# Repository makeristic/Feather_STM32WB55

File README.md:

# Feather STM32WB55

A KiCad design for an STM32WB55CGU6 Bluetooth development board in the Adafruit Feather form factor, with USB-C, STEMMA QT, optional QSPI flash, and an optional SWD debug connector.

## WARNING: Work In Progress

This is a work in progress, it may not work at all.  :)

**Do not order the included fabrication files as a manufacturing release.** The [source audit](docs/code-audit-report.md) corrected a D10-to-ground short in the PCB source; the historical Gerbers and drill files still predate that fix. Layout, footprint, stackup, and electrical/RF review remain necessary before regenerating a complete fabrication set.

## Overview

I have several [Adafruit Feather](https://www.adafruit.com/category/943) boards, and Adafruit handily publish the [Feather Specification](https://learn.adafruit.com/adafruit-feather/feather-specification) here to make your own.  

I recently discovered the STM32WB series of microcontrollers which include Bluetooth connectivity and decided to build my own development board around it.  This repository is my first attempt at designing it and builds upon the great work of several sources (see Acknowledgements below).

The ultimate goal is to get this board working and running [CircuitPython](https://circuitpython.org/), once working I may do another revision with a focus on enabling more of the low power features of the STM32WB series.

## Features

* [STM32WB55CGU6](https://www.st.com/en/microcontrollers-microprocessors/stm32wb55cg.html) microcontroller
* Adafruit Feather compatible, with USB-C
* (Optional) QSPI-Dual flash module can be soldered to the back
* (Optional) ARM SWD 10-pin debug connector can be soldered on the back

## Notes

* The original fabrication notes specify a 4-layer board, 1mm thick with impedance-controlled traces, assuming the standard JLCPCB stackup. The committed PCB file currently records a thickness of 1.6mm; resolve this discrepancy with the board stackup before ordering.
* I've tried to standardise on 0.2mm tracks for signals, 0.3mm tracks for power.  VBUS and +BATT do have high-current tracks/pours to their respective pins to allow for powering things off-board like Neopixels.
* STMicroelectronics produce a custom matching network for this microcontroller [MLPF-WB55-01E3](https://www.st.com/en/emi-filtering-and-signal-conditioning/mlpf-wb55-01e3.html), the recommended PCB layout has been implemented here.
* The [Fractus Antenna](https://fractusantennas.com/compact-reach-xtend-nn01-102/) has a recommended layout which is implemented here.  The clearance area essentially takes up the entire tip of the board, though I have cheekily added the STEMMA QT connector, figuring it shouldn't have too big an impact.
* There is a lot of space around the center of the board, this is semi-intentional so I can extend the design with sensors, or an additional button.
* You can find my custom footprints etc. here [Makeristic-KiCad-Library](https://github.com/makeristic/Makeristic-KiCad-Library)

## Repository contents

* [KiCad project](Feather_STM32WB55.pro), [legacy schematic](Feather_STM32WB55.sch), [PCB](Feather_STM32WB55.kicad_pcb), and [netlist](Feather_STM32WB55.net).
* [Schematic PDF](Feather_STM32WB55-schematic.pdf) and [bill of materials](Feather_STM32WB55-BOM.csv).
* [Gerber and drill exports](gerber/), including both inner copper layers.
* [STM32CubeMX configuration](cubemx/cubemx.ioc). This is configuration input, not a complete firmware application or a CircuitPython port.
* [Vendor datasheets and layout references](datasheets/) and [design images](images/).
* [Recovered STM32/switch libraries](libraries/), [historical symbol cache](Feather_STM32WB55-cache.lib), and project [symbol](sym-lib-table)/[footprint](fp-lib-table) tables.

## Open or modify the design

1. Clone the repository and open `Feather_STM32WB55.pro` in KiCad. The PCB records KiCad **5.1.7**; the `.pro` and `.sch` files are legacy formats. Import into a copy if using a newer KiCad release.
2. Install the corresponding KiCad standard libraries and clone the Makeristic library alongside this repository. The project tables resolve that sibling checkout and the recovered board-local STM32/switch libraries. Keep the committed cache with the schematic so historical symbols remain available.
3. Resolve library warnings before editing. ANT1 and FL1 now have qualified Makeristic footprint identifiers, and their 3D-model paths plus the STM32 model path resolve through the sibling checkout. The [library notes](libraries/README.md) describe the recovery and its limits; restored assets have not been independently redesigned or electrically verified.
4. Review the RF layout, power path, stackup, and design-rule results before fabrication. Refill zones after source edits, then regenerate exports only after resolving the [audit findings](docs/code-audit-report.md). Existing images and fabrication files remain historical snapshots.

Nightly KiCad netlist checks need the [audit's cache-only export procedure](docs/code-audit-report.md): globally resolving the legacy USB symbol in nightly 10.99.0 omitted its shield pin from the export. No symbol/wiring workaround or bulk format migration was applied.

CircuitPython support remains the original project goal. No application firmware, flashing guide, or electrical/RF test report is included, and successful operation is not established by the files in this repository.

## Schematic

## PCB

## 3D Render

## TODO

* Improve the layout, potentially reassigning GPIO pins to simplify the traces

## Acknowledgements

* [Adafruit](https://www.adafruit.com/)
* [YouTube: Phil's Lab](https://www.youtube.com/c/PhilS94/videos)

## Feedback and related projects

Use [Issues](https://github.com/makeristic/Feather_STM32WB55/issues) for questions, build reports, missing-library information, or design corrections. Include the commit, KiCad version, and relevant component references. For design pull requests, explain the circuit change and identify any regenerated fabrication files.

Related projects: [Feather USB-C template](https://github.com/makeristic/Adafruit_Feather_USB-C), [STUSB4500 breakout](https://github.com/makeristic/STUSB4500_Breakout), and [Makeristic-KiCad-Library](https://github.com/makeristic/Makeristic-KiCad-Library).

## Licence

Michael Cutler's original design work and documentation are available under the [MIT licence](LICENSE). Vendor PDFs in `datasheets/`, third-party symbols, footprints and models (including embedded, recovered, and cached library elements), and third-party marks retain their respective owners' terms. KiCad symbols retain [CC BY-SA 4.0 with the KiCad exception](LICENSES/KiCad-Libraries.md). The MIT grant does not relicense those materials or imply endorsement by the acknowledged organisations.

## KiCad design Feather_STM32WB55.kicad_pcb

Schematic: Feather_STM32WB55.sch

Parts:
ANT1: NN01-102; FR05S1N0102; Manufacturer_Part_Number FR05-S1-N-0-102; Mouser Part Number 128-FR05-S1-N-0-102
C1, C2, C3: 10u; C_0805_2012Metric
C4: 1u; C_0805_2012Metric
C5: 1u; C_0603_1608Metric
C6: 10n; C_0603_1608Metric
C7: 4u7; C_0805_2012Metric
C8, C9, C10, C11, C12, C13: 100n; C_0603_1608Metric
C14: 100p; C_0603_1608Metric
D1, D4: LED; LED_0603_1608Metric
D2: B5819W; D_SOD-123; LCSC Part # C8598
D3: WS2812B; LED_SK6812MINI_PLCC4_3.5x3.5mm_P1.75mm
FL1: MLPF-WB55-01E3; MLPFWB5501E3; Manufacturer_Part_Number MLPF-WB55-01E3; Mouser Part Number 511-MLPF-WB55-01E3
J1: JST-SH Qwiic; JST_SH_SM04B-SRSS-TB_1x04-1MP_P1.00mm_Horizontal
J2: Conn_Battery; JST_PH_S2B-PH-SM4-TB_1x02-1MP_P2.00mm_Horizontal; Manufacturer Part # S2B-PH-SM4-TB(LF)(SN); LCSC Part # C295747
J3: Conn_ARM_JTAG_SWD_10; PinHeader_2x05_P1.00mm_Vertical_SMD
J4: Conn_Right; PinHeader_1x12_P2.54mm_Vertical
J5: USB_C_Receptacle_USB2.0; USB_C_Receptacle_XKB_U262-16XN-4BVC11; Manufacturer Part # U262-161N-4BVC11; LCSC Part # C319148
J6: Conn_Left; PinHeader_1x16_P2.54mm_Vertical
L1: 39n; L_0603_1608Metric
Q1: NTR4171PT1G; SOT-23; Manufacturer Part # NTR4171PT1G; LCSC Part # C558218
R1, R4: 1k; R_0603_1608Metric
R2, R3, R5: 10k; R_0603_1608Metric
R6, R10: 100k; R_0603_1608Metric
R7, R8, R9: 5k1; R_0603_1608Metric
SW1: SMD-BUTTON-TOP-DHT-4235A_4P-4.2X3.2MM_; SW4-SMD-4.2X3.2X2.5MM; MPN DHT-4235A
U1: MCP73831-2-OT; SOT-23-5
U2: AP2112K-3.3; SOT-23-5
U3: STM32WB55CGU6; STMicroelectronics-STM32WB55CGU6-IPC_B; mouser part number 511-STM32WB55CGU6; digikey description ULTRA-LOW-POWER DUAL CORE ARM CO
U4: USBLC6-2SC6; SOT-23-6
U5: Flash SOIC-8; SOIC-8_3.9x4.9mm_P1.27mm
Y1: 32Mhz; Crystal_SMD_3225-4Pin_3.2x2.5mm; Manufacturer Part # X1E000021016300; LCSC Part # C91742

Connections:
+3.3VA: C5.1, C6.1, J6.3, L1.1, U3.8 (VDDA)
+BATT: C1.1, J2.2, J4.1, Q1.3 (D), U1.3 (VBAT)
A0: J6.5, U3.43 (PB3)
A1: J6.6, U3.2 (PC14-OSC32_IN)
A2: J6.7, U3.3 (PC15-OSC32_OUT)
A3: J6.8, U3.9 (PA0)
A4: J6.9, U3.13 (PA4)
A5: J6.10, U3.14 (PA5)
ANT_OUT: ANT1.1, FL1.1
BOOT0: J6.16, R10.1, U3.4 (PH3-BOOT0)
D5: J4.10, U3.28 (PB0)
D6: J4.9, U3.29 (PB1)
D8_NEOPIXEL: D3.4 (DIN), U3.42 (PA15)
D9: J4.8, U3.30 (PE4)
D10: J4.7, U3.19 (PB2)
D11: J4.6, U3.17 (PA8)
D12: J4.5, U3.16 (PA7)
D13: J4.4, R4.1, U3.15 (PA6)
EN: J4.2, R5.2, U2.3 (EN)
GND: C1.2, C2.2, C3.2, C4.2, C5.2, C6.2, C7.2, C8.2, C9.2, C10.2, C11.2, C12.2, C13.2, C14.2, D3.3 (VSS), D4.1 (K), FL1.2, FL1.4, FL1.5, FL1.6, J1.1, J2.1, J3.3 (GND), J3.5 (GND), J3.9 (GNDDetect), J5.A1 (GND), J5.A12 (GND), J5.B1 (GND), J5.B12 (GND), J5.S1 (SHIELD), J6.4, R6.2, R7.2, R8.2, R9.2, R10.2, SW1.3 (B0), SW1.4 (B1), U1.2 (VSS), U2.2 (GND), U3.22 (VSSRF), U3.32 (VSSSMPS), U3.49 (EP), U4.2 (GND), U5.4 (GND), Y1.2, Y1.4
HSE_IN: U3.25 (OSC_IN), Y1.1
HSE_OUT: U3.24 (OSC_OUT), Y1.3
I2C_SCL: J1.4, J4.11, R2.2, U3.18 (PA9)
I2C_SDA: J1.3, J4.12, R3.2, U3.36 (PA10)
NRST: J3.10 (~RESET~), J6.1, SW1.1 (A0), SW1.2 (A1), U3.7 (~RST~)
unnamed: C2.1, D2.1 (K), Q1.2 (S), R5.1, U2.1 (VIN)
unnamed: D1.1 (K), R1.1
unnamed: D4.2 (A), R4.2
unnamed: J5.A5 (CC1), R9.1
unnamed: J5.B5 (CC2), R8.1
unnamed: R1.2, U1.1 (STAT)
unnamed: R7.1, U1.5 (PROG)
QSPI_CLK: U3.12 (PA3), U5.6 (SCK)
QSPI_IO0: U3.6 (PB9), U5.5 (SI/IO0)
QSPI_IO1: U3.5 (PB8), U5.2 (SO/IO1)
QSPI_NSC: U3.11 (PA2), U5.1 (~CS)
RF_OUT: FL1.3, U3.21 (RF1)
SPI_MISO: J6.13, U3.44 (PB4)
SPI_MOSI: J6.12, U3.45 (PB5)
SPI_SCK: J6.11, U3.10 (PA1)
SWDCLK: J3.4 (SWDCLK/TCK), U3.41 (PA14)
SWDIO: J3.2 (SWDIO/TMS), U3.39 (PA13)
USART1_RX: J6.14, U3.47 (PB7)
USART1_TX: J6.15, U3.46 (PB6)
USB_CONN_D+: J5.A6 (D+), J5.B6 (D+), U4.3 (I/O2)
USB_CONN_D-: J5.A7 (D-), J5.B7 (D-), U4.1 (I/O1)
USB_D+: U3.38 (PA12), U4.4 (I/O2)
USB_D-: U3.37 (PA11), U4.6 (I/O1)
VBUS: D1.2 (A), D2.2 (A), J4.3, J5.A4 (VBUS), J5.A9 (VBUS), J5.B4 (VBUS), J5.B9 (VBUS), Q1.1 (G), R6.1, U1.4 (VDD), U4.5 (VBUS)
VDD: C3.1, C4.1, C7.1, C8.1, C9.1, C10.1, C11.1, C12.1, C13.1, C14.1, D3.1 (VDD), J1.2, J3.1 (VTref), J6.2, L1.2, R2.1, R3.1, U2.5 (VOUT), U3.1 (VBAT), U3.20 (VDD), U3.23 (VDDRF), U3.31 (VFBSMPS), U3.33 (VLXSMPS), U3.34 (VDDSMPS), U3.35 (VDD), U3.40 (VDDUSB), U3.48 (VDD), U5.3 (~WP~/IO2), U5.7 (~HOLD~/IO3), U5.8 (VCC)

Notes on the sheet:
Connectors etc.
Microcontroller
Power
Misc

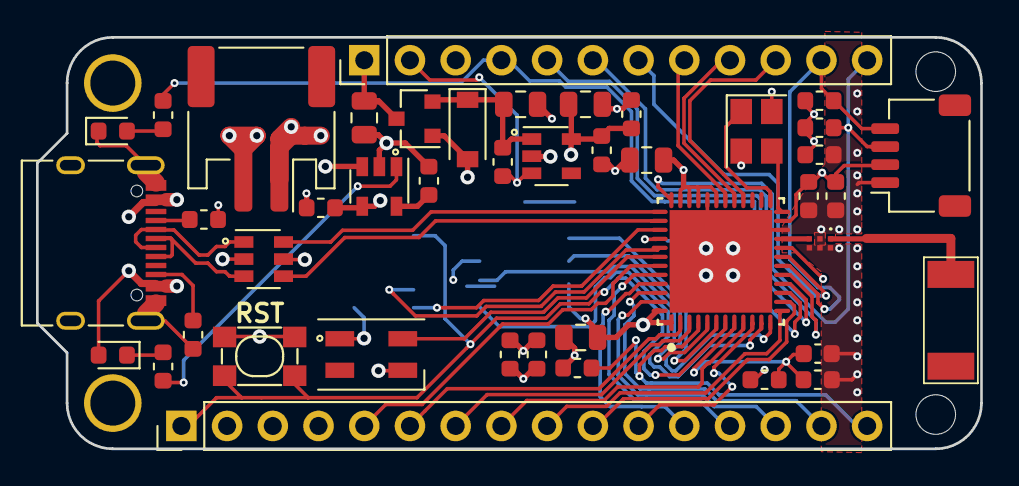
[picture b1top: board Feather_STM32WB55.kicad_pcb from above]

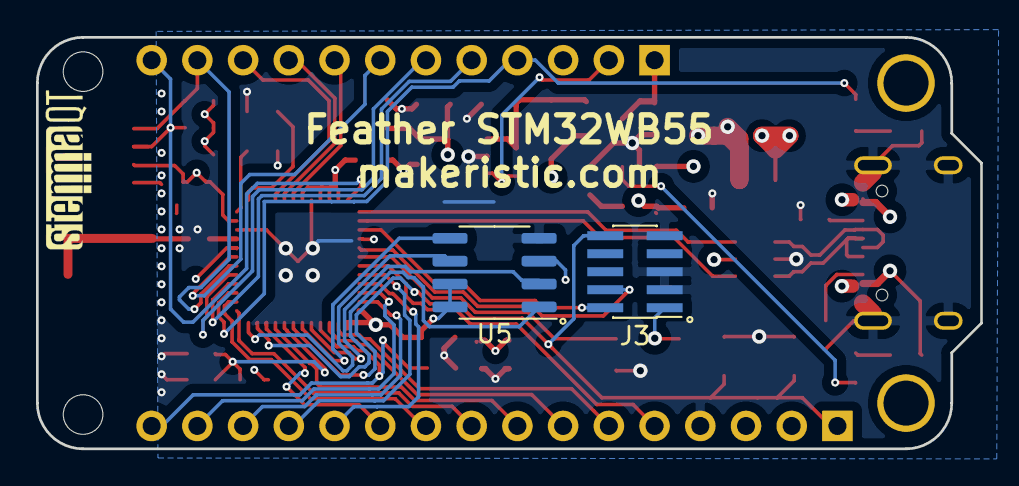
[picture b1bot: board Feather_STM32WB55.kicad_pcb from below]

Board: 4 copper layers, 52.5 x 22.9 mm, 45 parts (2 on the bottom side), 50 nets.

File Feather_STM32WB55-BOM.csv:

Reference, Value, Footprint, Datasheet, LCSC Part #, Manufacturer Part #, RAM size, ambient temperature range high, ambient temperature range low, automotive, category, core architecture, data bus width, device class L1, device class L2, device class L3, digikey description, digikey part number, frequency, height, interface, lead free, library id, manufacturer, max junction temp, max supply voltage, memory size, memory type, min supply voltage, mouser part number, number of A/D converters, number of ADC channels, number of I/Os, number of I2C channels, number of PWM channels, number of SPI channels, number of UART channels, number of USB channels, number of cores, number of timers/counters, package, rohs, standoff height, temperature range high, temperature range low, MPN, SKU, Description, Height, Manufacturer_Name, Manufacturer_Part_Number, Mouser Part Number, Mouser Price/Stock, Arrow Part Number, Arrow Price/Stock
"J4","Conn_Right","Connector_PinHeader_2.54mm:PinHeader_1x12_P2.54mm_Vertical","~"
"J6","Conn_Left","Connector_PinHeader_2.54mm:PinHeader_1x16_P2.54mm_Vertical","~"
"J2","Conn_Battery","Connector_JST:JST_PH_S2B-PH-SM4-TB_1x02-1MP_P2.00mm_Horizontal","https://datasheet.lcsc.com/szlcsc/2004071131_JST-Sales-Ameri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","C295747","S2B-PH-SM4-TB(LF)(SN)","","","","","","","","","","","","","","","","","","","","","","","","","","","","","","","","","","","","","","","","","","","","","","","","",""
"J5","USB_C_Receptacle_USB2.0","Connector_USB:USB_C_Receptacle_XKB_U262-16XN-4BVC11","https://datasheet.lcsc.com/szlcsc/2002271811_XKB-Enterprise-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","C319148","U262-161N-4BVC11","","","","","","","","","","","","","","","","","","","","","","","","","","","","","","","","","","","","","","","","","","","","","","","","",""
"U3","STM32WB55CGU6","IC_STMicroelectronics_STM32WB55CGU6:STMicroelectronics-STM32WB55CGU6-IPC_B","https://www.st.com/resource/en/datasheet/stm32wb55cg.pdf","","","256KBytes","+85°C","-40°C","No","IC","ARM Cortex-M4","32bits","Integrated Circuits (ICs)","Embedded Processors and Controllers","Microcontrollers","ULTRA-LOW-POWER DUAL CORE ARM CO","497-18489-ND","64MHz","0.65mm","I2C,SPI,UART,USART,2-Wire,USB,IrDA,Other","Yes","7cd8443577175ffa","STMicroelectronics","+105°C","3.6V","1MBytes","FLASH","1.71V","511-STM32WB55CGU6","1","13","30","2","14","1","2","1","1","6","UFQFPN48","Yes","0mm","+105°C","-40°C","","","","","","","","","",""
"J3","Conn_ARM_JTAG_SWD_10","Connector_PinHeader_1.00mm:PinHeader_2x05_P1.00mm_Vertical_SMD","http://infocenter.arm.com/help/topic/com.arm.doc.ddi0314h/DD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"
"U4","USBLC6-2SC6","Package_TO_SOT_SMD:SOT-23-6","https://www.st.com/resource/en/datasheet/usblc6-2.pdf"
"C13","100n","Capacitor_SMD:C_0603_1608Metric","~"
"Y1","32Mhz","Crystal:Crystal_SMD_3225-4Pin_3.2x2.5mm","https://datasheet.lcsc.com/szlcsc/Seiko-Epson-X1E00002101630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","C91742","X1E000021016300","","","","","","","","","","","","","","","","","","","","","","","","","","","","","","","","","","","","","","","","","","","","","","","","",""
"L1","39n","Inductor_SMD:L_0603_1608Metric","~"
"C5","1u","Capacitor_SMD:C_0603_1608Metric","~"
"C6","10n","Capacitor_SMD:C_0603_1608Metric","~"
"C7","4u7","Capacitor_SMD:C_0805_2012Metric","~"
"C8","100n","Capacitor_SMD:C_0603_1608Metric","~"
"C9","100n","Capacitor_SMD:C_0603_1608Metric","~"
"C10","100n","Capacitor_SMD:C_0603_1608Metric","~"
"C11","100n","Capacitor_SMD:C_0603_1608Metric","~"
"C12","100n","Capacitor_SMD:C_0603_1608Metric","~"
"C14","100p","Capacitor_SMD:C_0603_1608Metric","~"
"U2","AP2112K-3.3","Package_TO_SOT_SMD:SOT-23-5","https://www.diodes.com/assets/Datasheets/AP2112.pdf"
"R5","10k","Resistor_SMD:R_0603_1608Metric","~"
"Q1","NTR4171PT1G","Package_TO_SOT_SMD:SOT-23","https://datasheet.lcsc.com/szlcsc/2005221838_VBsemi-Elec-NTR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","C558218","NTR4171PT1G","","","","","","","","","","","","","","","","","","","","","","","","","","","","","","","","","","","","","","","","","","","","","","","","",""
"C2","10u","Capacitor_SMD:C_0805_2012Metric","~"
"C3","10u","Capacitor_SMD:C_0805_2012Metric","~"
"C4","1u","Capacitor_SMD:C_0805_2012Metric","~"
"U1","MCP73831-2-OT","Package_TO_SOT_SMD:SOT-23-5","http://ww1.microchip.com/downloads/en/DeviceDoc/20001984g.pdf"
"C1","10u","Capacitor_SMD:C_0805_2012Metric","~"
"R7","5k1","Resistor_SMD:R_0603_1608Metric","~"
"R1","1k","Resistor_SMD:R_0603_1608Metric","~"
"D1","LED","LED_SMD:LED_0603_1608Metric","~"
"R8","5k1","Resistor_SMD:R_0603_1608Metric","~"
"R9","5k1","Resistor_SMD:R_0603_1608Metric","~"
"D3","WS2812B","LED_SMD:LED_SK6812MINI_PLCC4_3.5x3.5mm_P1.75mm","https://cdn-shop.adafruit.com/datasheets/WS2812B.pdf"
"R4","1k","Resistor_SMD:R_0603_1608Metric","~"
"D4","LED","LED_SMD:LED_0603_1608Metric","~"
"J1","JST-SH Qwiic","Connector_JST:JST_SH_SM04B-SRSS-TB_1x04-1MP_P1.00mm_Horizontal","~"
"R2","10k","Resistor_SMD:R_0603_1608Metric","~"
"R3","10k","Resistor_SMD:R_0603_1608Metric","~"
"R10","100k","Resistor_SMD:R_0603_1608Metric","~"
"U5","Flash SOIC-8","Package_SO:SOIC-8_3.9x4.9mm_P1.27mm","https://www.adestotech.com/wp-content/uploads/DS-AT25SF081_045.pdf"
"D2","B5819W","Diode_SMD:D_SOD-123","https://datasheet.lcsc.com/szlcsc/1809140216_Changjiang-Elec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","C8598","","","","","","","","","","","","","","","","","","","","","","","","","","","","","","","","","","","","","","","","","","","","","","","","","",""
"R6","100k","Resistor_SMD:R_0603_1608Metric","~"
"SW1","SMD-BUTTON-TOP-DHT-4235A_4P-4.2X3.2MM_","OPL_Switch:SW4-SMD-4.2X3.2X2.5MM","","","","","","","","","","","","","","","","","","","","","","","","","","","","","","","","","","","","","","","","","","","DHT-4235A","311020045","","","","","","","",""
"ANT1","NN01-102","FR05S1N0102","https://www.fractusantennas.com/files/UM_FR05_S1_N_0_102.pdf","","","","","","","","","","","","","","","","","","","","","","","","","","","","","","","","","","","","","","","","","","","","Compact Reach XtendTM (FR05-S1-N-0-102)  Bluetooth, Zigbee, 802.11 b/g/n WLAN","2.2","Fractus Antennas","FR05-S1-N-0-102","128-FR05-S1-N-0-102","https://www.mouser.co.uk/ProductDetail/Fractus-Antennas/FR05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","",""
"FL1","MLPF-WB55-01E3","MLPFWB5501E3","https://www.st.com/resource/en/datasheet/mlpf-wb55-01e3.pdf","","","","","","","","","","","","","","","","","","","","","","","","","","","","","","","","","","","","","","","","","","","","RF Wireless Misc 2.4 GHz Low Pass Filter matched to STM32WB55","0.7","STMicroelectronics","MLPF-WB55-01E3","511-MLPF-WB55-01E3","https://www.mouser.co.uk/ProductDetail/STMicroelectronics/ML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","MLPF-WB55-01E3","https://www.arrow.com/en/products/mlpf-wb55-01e3/stmicroelectronics"

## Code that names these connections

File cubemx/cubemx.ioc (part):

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Mcu.Name=STM32WB55CGUx
Mcu.Package=UFQFPN48
Mcu.UserName=STM32WB55CGUx
PA0.Signal=GPIO_Analog
PA1.Mode=Full_Duplex_Master
PA1.Signal=SPI1_SCK
PA10.Mode=I2C
PA10.Signal=I2C1_SDA
PA11.Mode=Device
PA11.Signal=USB_DM
PA12.Mode=Device
PA12.Signal=USB_DP
PA13.Mode=Serial_Wire
PA13.Signal=SYS_JTMS-SWDIO
PA14.Mode=Serial_Wire
PA14.Signal=SYS_JTCK-SWCLK
PA15.Signal=GPIO_Output
PA2.Mode=Single Bank 1 2IOs
PA2.Signal=QUADSPI_BK1_NCS
PA3.Mode=Single Bank 1 2IOs
PA3.Signal=QUADSPI_CLK
PA4.Signal=GPIO_Analog
PA5.Signal=GPIO_Analog
PA6.Signal=GPIO_Output
PA7.Signal=GPIO_Output
PA8.Signal=GPIO_Analog
PA9.Mode=I2C
PA9.Signal=I2C1_SCL
PB0.Signal=GPIO_Output
PB1.Signal=GPIO_Analog
PB2.Signal=GPIO_Analog
PB3.Signal=GPIO_Output
PB4.Mode=Full_Duplex_Master
PB4.Signal=SPI1_MISO
PB5.Mode=Full_Duplex_Master
PB5.Signal=SPI1_MOSI
PB6.Mode=Asynchronous
PB6.Signal=USART1_TX
PB7.Mode=Asynchronous
PB7.Signal=USART1_RX
PB8.Mode=Single Bank 1 2IOs
PB8.Signal=QUADSPI_BK1_IO1
PB9.Mode=Single Bank 1 2IOs
PB9.Signal=QUADSPI_BK1_IO0
PC14-OSC32_IN.Signal=GPIO_Output
PC15-OSC32_OUT.Signal=GPIO_Output
PE4.Signal=GPIO_Output
PH3-BOOT0.Signal=GPIO_Input
RCC.HSE_VALUE=32000000
RCC.SYSCLKFreq_VALUE=64000000
RCC.SYSCLKSource=RCC_SYSCLKSOURCE_PLLCLK
board=custom

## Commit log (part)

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2020-10-13 Removing caches
2020-10-13 Added images
2020-10-14 Added 3D images
2020-10-14 Removed copper fill on F.Cu updated the PCB images
2020-10-15 Updated with the matching network and antenna
2020-10-21 Updated ready for manufacturing
2020-10-24 v1.1 work in progress
2020-10-24 Updated image
2020-10-24 Tidied up the power section, rearranged components, standardised traces to 0.3mm for power lines, 0.2mm for data lines
2020-10-24 More tidying up of traces and silkscreen
2020-10-24 OCD moving traces around
2020-10-24 Updated images
2020-10-24 Updated gerbers
